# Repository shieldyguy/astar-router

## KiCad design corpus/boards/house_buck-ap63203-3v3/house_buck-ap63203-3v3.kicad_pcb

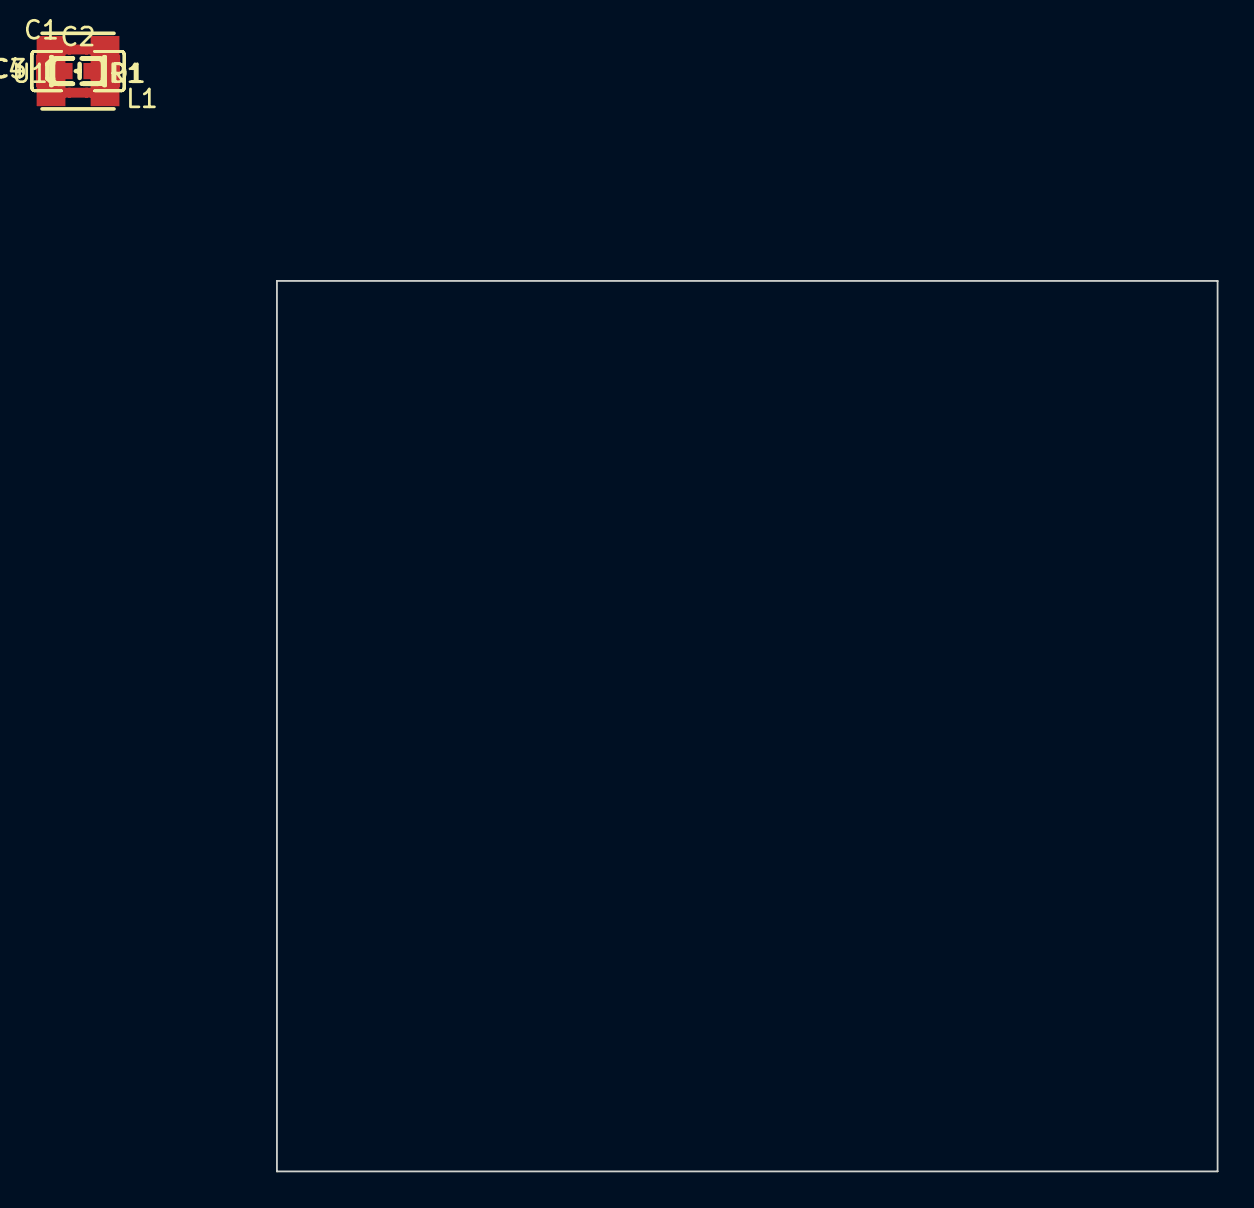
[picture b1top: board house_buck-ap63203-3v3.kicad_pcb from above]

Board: 2 copper layers, 52.3 x 49.5 mm, 8 parts (0 on the bottom side), 6 nets, no tracks yet.

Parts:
C1, C3, C4: 22uF; CL31A226KAHNNNE
C2: 100nF; CC0603KRX7R9BB104
D1: 3V3; KT-0603R
L1: 4.7uH; FNR4030S4R7MT
R1: 10kΩ; 0603WAF1002T5E
U1: AP63203; AP63203WU-7

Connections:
+3V3: C3.1, C4.1, L1.2, R1.1, U1.1 (FB)
GND: C1.2, C3.2, C4.2, D1.2, U1.4 (GND)
unnamed: D1.1, R1.2
unnamed: C2.1, U1.6 (BST)
unnamed: C2.2, L1.1, U1.5 (SW)
VIN: C1.1, U1.2 (EN), U1.3 (VIN)

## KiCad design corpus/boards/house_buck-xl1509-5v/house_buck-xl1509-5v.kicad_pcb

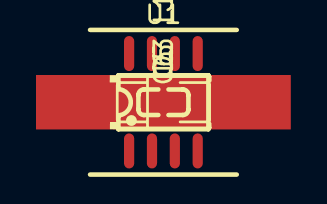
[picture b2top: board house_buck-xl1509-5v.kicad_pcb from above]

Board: 2 copper layers, 5 parts (0 on the bottom side), 3 nets, no tracks yet.

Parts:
C5: 10uF; CL31B106KBHNNNE
C6: 100nF; CC0603KRX7R9BB104
D3: SS34
L1: 100uH; YNR8040-101M
U1: XL1509-5.0; XL1509-5.0E1

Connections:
+5V: C5.1, C6.1, L1.2, U1.3
GND: C5.2, C6.2, D3.2, U1.4, U1.5, U1.6, U1.7, U1.8
unnamed: D3.1, L1.1, U1.2

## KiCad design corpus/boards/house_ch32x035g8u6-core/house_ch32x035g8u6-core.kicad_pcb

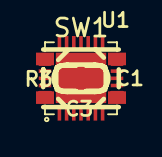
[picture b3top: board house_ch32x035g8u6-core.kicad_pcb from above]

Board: 2 copper layers, 5 parts (0 on the bottom side), 4 nets, no tracks yet.

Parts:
C1: 100nF; CC0603KRX7R9BB104
C3: 10uF; CL10A106MA8NRNC
R3: 5.1kΩ; 0603WAF5101T5E
SW1: BOOT; GT-TC048D-H025-L1
U1: CH32X035G8U6

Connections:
+5V: C1.1, C3.1, SW1.3, U1.2
GND: C1.2, C3.2, U1.29
unnamed: R3.2, SW1.1
USB_DP: R3.1, U1.27

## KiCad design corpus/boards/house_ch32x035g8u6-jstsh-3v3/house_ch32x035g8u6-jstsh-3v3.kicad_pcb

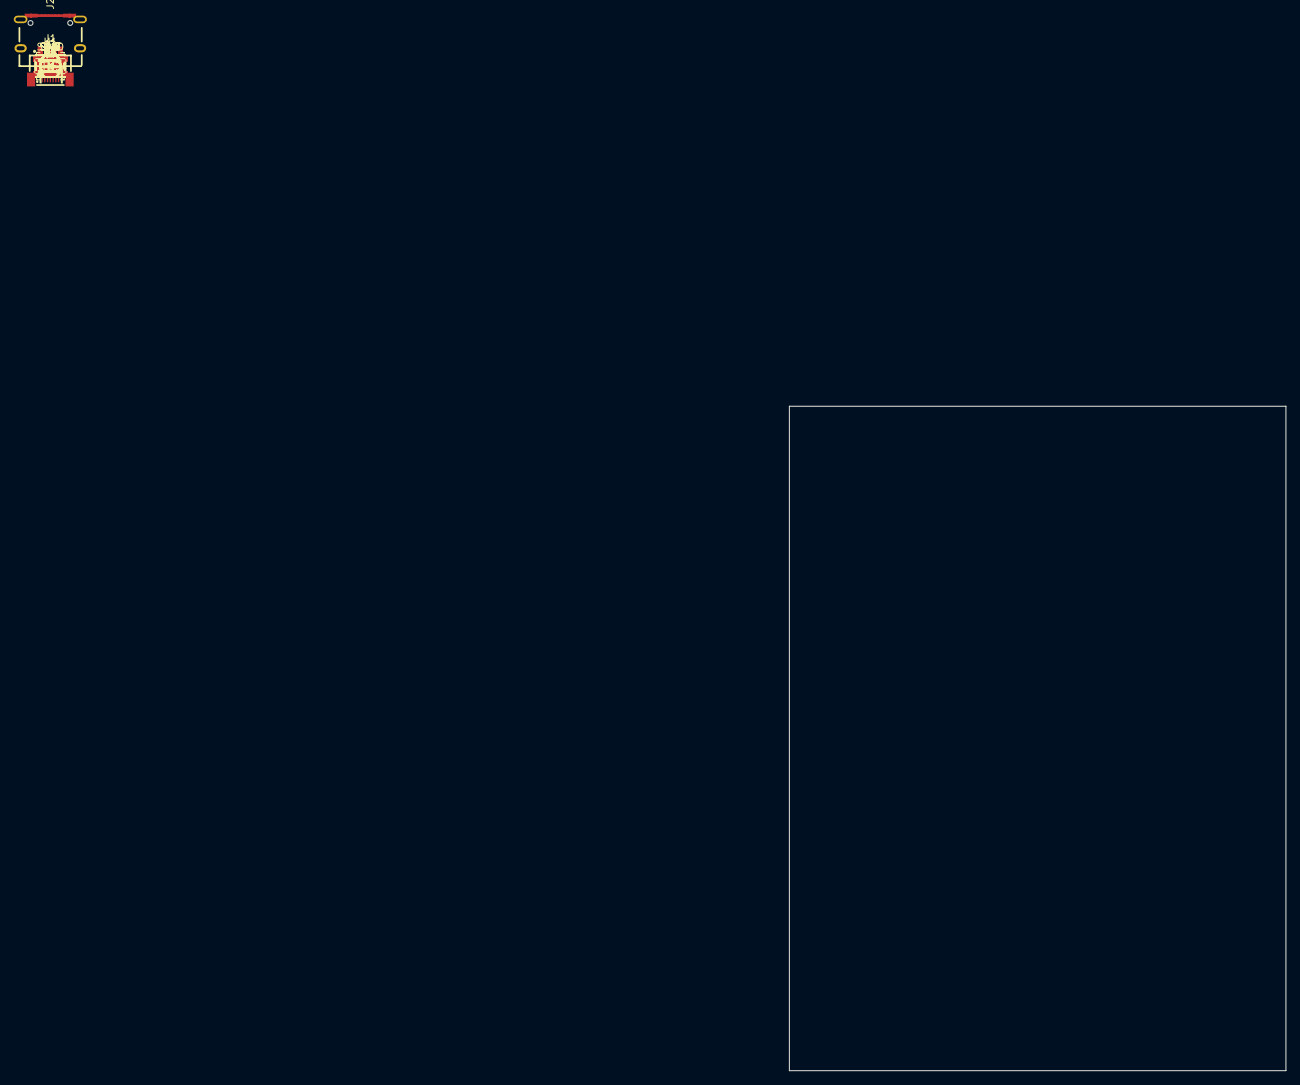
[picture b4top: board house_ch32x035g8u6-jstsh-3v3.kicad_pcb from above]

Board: 2 copper layers, 72.3 x 96.7 mm, 23 parts (0 on the bottom side), 23 nets, no tracks yet.

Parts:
C1: 100nF; CC0603KRX7R9BB104
C3: 10uF; CL10A106MA8NRNC
C4: 1uF; CL10A105KB8NNNC
D1, D2: B5819W SL; B5819W_SL
F1: JK-nSMD050-30
J1: PWR; 1.0-4PWB
J2: USB-C; TYPE-C_16PIN_2MD(073)
R3, R4, R5: 5.1kΩ; 0603WAF5101T5E
SW2: BTN1; GT-TC048D-H025-L1
SW3: BTN2; GT-TC048D-H025-L1
SW4: BTN3; GT-TC048D-H025-L1
SW5: BTN4; GT-TC048D-H025-L1
SW6: BTN5; GT-TC048D-H025-L1
SW7: BTN6; GT-TC048D-H025-L1
SW8: BTN7; GT-TC048D-H025-L1
SW9: BTN8; GT-TC048D-H025-L1
SW10: BOOT; GT-TC048D-H025-L1
U1: CH32X035G8U6
U2: LP5907MFX-3.3/NOPB; LP5907MFX-3.3_NOPB
U3: USBLC6-2SC6

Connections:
+3V3: C1.1, C3.1, D2.1, SW10.2, U1.2 (VDD), U2.5 (OUT)
BTN1: SW2.1, U1.14 (PB3/TX3/T2C3_/T2C3N_/O2P1)
BTN2: SW3.1, U1.15 (PB4/T2C4_/T3C1_/T2BK_/RX3/O1P2)
BTN3: SW4.1, U1.17 (PB6/T1C1N/CTS3/O1N1)
BTN4: SW5.1, U1.18 (PB7/T1C2N/RTS3_/O2P2)
BTN5: SW6.1, U1.19 (PB8/T1C3N/O1P1)
BTN6: SW7.1, U1.20 (PB9/T1C1/MCO/TX4_)
BTN7: SW8.1, U1.28 (PC14/CC1/T1C3_/T2C2_)
BTN8: SW9.1, U1.1 (PC15/CC2/T2C3_/T1ET_)
GND: C1.2, C3.2, C4.2, J1.4, J2.13 (EH), J2.14 (EH), J2.A1B12 (GND), J2.B1A12 (GND), R4.2, R5.2, SW2.3, SW3.3, SW4.3, SW5.3, SW6.3, SW7.3, SW8.3, SW9.3, U1.29 (GND), U2.2 (GND), U3.2
unnamed: D1.2, F1.2
unnamed: D2.2, J1.1
unnamed: J2.A5 (CC1), R4.1
unnamed: J2.B5 (CC2), R5.1
unnamed: R3.2, SW10.4
U1RX: J1.3, U1.22 (PB11/T1C3/T2C1N_/RX1)
U1TX: J1.2, U1.21 (PB10/TX1/T1C2)
USB_DM: U1.26 (PC16/UDM/T1C4/TX4_/I2C_/RX4_/CTS1/PC11), U3.6
USB_DM_C: J2.A7 (Dn1), J2.B7 (Dn2), U3.1
USB_DP: R3.1, U1.27 (PC17/UDP/RTS1/TX4_/I2C_/RX4_/T1ET/PC10), U3.4
USB_DP_C: J2.A6 (Dp1), J2.B6 (Dp2), U3.3
VBUS_C: F1.1, J2.A4B9 (VBUS), J2.B4A9 (VBUS), U3.5
VIN: C4.1, D1.1, U2.1 (IN), U2.3 (EN)

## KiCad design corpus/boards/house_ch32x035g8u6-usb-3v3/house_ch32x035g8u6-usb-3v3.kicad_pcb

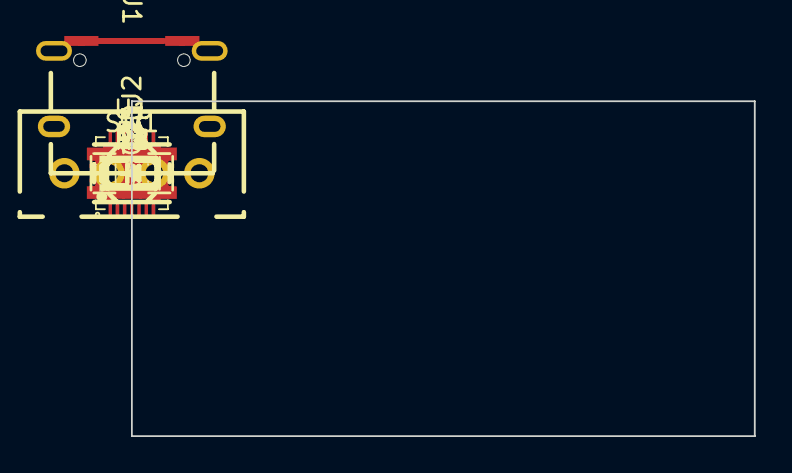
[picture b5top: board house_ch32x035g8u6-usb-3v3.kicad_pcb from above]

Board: 2 copper layers, 34.6 x 18.6 mm, 15 parts (0 on the bottom side), 16 nets, no tracks yet.

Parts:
C1: 10uF; CL10A106MA8NRNC
C2: 1uF; CL10A105KB8NNNC
D1: B5819W SL; B5819W_SL
D2: RUN; KT-0603R
F1: JK-nSMD050-30
J1: USB-C; TYPE-C_16PIN_2MD(073)
J2: DEBUG; B4B-XH-A(LF)(SN)
R1, R2, R3: 5.1kΩ; 0603WAF5101T5E
R4: 1kΩ; 0603WAF1001T5E
SW1: BOOT; GT-TC048D-H025-L1
U1: CH32X035G8U6
U2: USBLC6-2SC6
U3: LP5907MFX-3.3/NOPB; LP5907MFX-3.3_NOPB

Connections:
+3V3: C1.1, J2.1, SW1.3, U1.2, U3.5
+5V: C2.1, D1.1, U3.1, U3.3
GND: C1.2, C2.2, D2.2, J1.13, J1.14, J1.A1B12, J1.B1A12, J2.4, R2.2, R3.2, U1.29, U2.2, U3.2
unnamed: D1.2, F1.2
unnamed: D2.1, R4.2
unnamed: J1.A5, R2.1
unnamed: J1.B5, R3.1
unnamed: J1.A7, J1.B7, U2.1
unnamed: J1.A6, J1.B6, U2.3
unnamed: R1.2, SW1.1
unnamed: R4.1, U1.23
SWCLK: J2.3, U1.24
SWDIO: J2.2, U1.25
USB_DM: U1.26, U2.6
USB_DP: R1.1, U1.27, U2.4
VBUS_C: F1.1, J1.A4B9, J1.B4A9, U2.5

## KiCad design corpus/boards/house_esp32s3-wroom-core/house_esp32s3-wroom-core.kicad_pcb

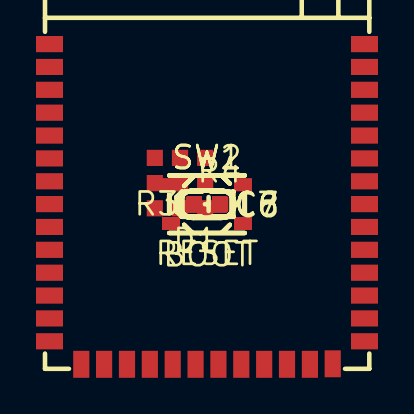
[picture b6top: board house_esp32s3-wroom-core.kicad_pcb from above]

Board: 2 copper layers, 9 parts (0 on the bottom side), 6 nets, no tracks yet.

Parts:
C6: 10uF; CL10A106MA8NRNC
C7: 100nF; CC0603KRX7R9BB104
C8: 1uF; CL10A105KB8NNNC
D1: RUN; KT-0603R
R3: 10kΩ; 0603WAF1002T5E
R4: 1kΩ; 0603WAF1001T5E
SW1: RESET; GT-TC048D-H025-L1
SW2: BOOT; GT-TC048D-H025-L1
U1: ESP32-S3; ESP32-S3-WROOM-1-N16R8

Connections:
+3V3: C6.1, C7.1, R3.1, U1.2 (3V3)
GND: C6.2, C7.2, C8.2, D1.2, SW1.3, SW2.3, U1.1 (GND), U1.40 (GND), U1.41 (GND)
unnamed: D1.1, R4.2
unnamed: C8.1, R3.2, SW1.1, U1.3 (EN)
unnamed: SW2.1, U1.27 (IO0)
unnamed: R4.1, U1.25 (IO48)

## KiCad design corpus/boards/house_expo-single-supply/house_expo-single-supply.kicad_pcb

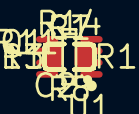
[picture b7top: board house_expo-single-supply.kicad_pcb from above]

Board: 2 copper layers, 11 parts (0 on the bottom side), 9 nets, no tracks yet.

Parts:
C1: 100nF; C0603
C2: 30pF; C0603
Q1: PAIR; SOT-363_L2.0-W1.3-P0.65-LS2.1-BR
R1: 4.7MΩ; R0603
R7, R8, R12, R14: 100kΩ; R0603
R11: 18kΩ; R0603
R13: 1.8kΩ; R0603
U1: TLV9152; SOT-23-8_L3.0-W1.7-P0.65-LS2.8-BR

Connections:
GND: C1.2, R1.1, U1.4
unnamed: C2.1, R11.1, U1.7
unnamed: C2.2, Q1.3, R1.2, U1.6
unnamed: Q1.1, R12.1, R13.2
unnamed: Q1.4, Q1.5, R11.2
unnamed: R12.2, R14.1, U1.1
unnamed: R7.2, R8.2, R14.2, U1.2
VCC: C1.1, U1.8
VREF: Q1.2, R13.1, U1.3, U1.5

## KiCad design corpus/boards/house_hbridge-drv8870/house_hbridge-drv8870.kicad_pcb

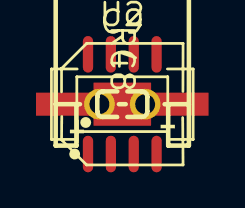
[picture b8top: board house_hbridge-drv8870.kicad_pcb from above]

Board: 2 copper layers, 5 parts (0 on the bottom side), 5 nets, no tracks yet.

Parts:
C8: 100nF; CC0603KRX7R9BB104
C9: 100uF; RVT1H101M0607
J2: MOTOR; S2B-XH-A(LF)(SN)
R4: 20mΩ; 25121WF200MT4E
U2: DRV8870DDAR

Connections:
+24V: C8.1, C9.1, U2.5
/M1_ISEN: R4.1, U2.7
/M1_OUT1: J2.1, U2.6
/M1_OUT2: J2.2, U2.8
GND: C8.2, C9.2, R4.2, U2.1, U2.9
